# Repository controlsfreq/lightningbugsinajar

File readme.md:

# Readme #

The Lightning Bugs in a Jar (LBJ) application is used to control up to 8 LEDs and flash them randomly as if they were lightning bugs.

## Toolchain ##

* [WinAVR](http://sourceforge.net/projects/winavr/files/) - Compiler, linker, archiver, etc.
* [AvrDude](http://www.nongnu.org/avrdude/) - Programmer interface application.
* [LibUSB](http://sourceforge.net/projects/libusb-win32/) - USB driver for AvrDude which allows it to interface with the AVRISP mkII. Running `bin/inf-wizard.exe` will create a driver for a connected AVRISP mkII and install it.
* [Cygwin](https://www.cygwin.com) - Provides Make and a build environment.

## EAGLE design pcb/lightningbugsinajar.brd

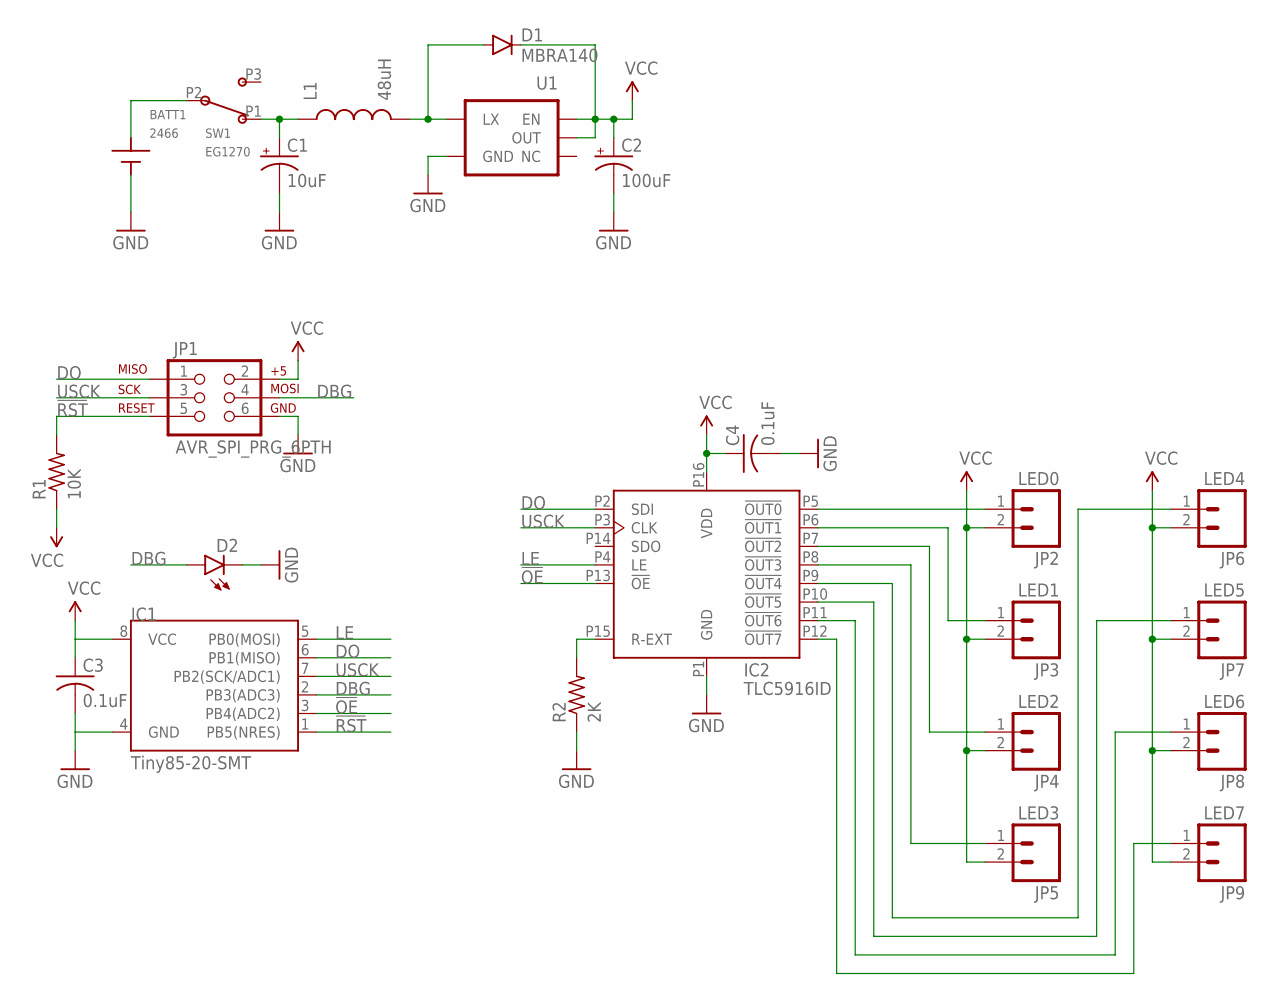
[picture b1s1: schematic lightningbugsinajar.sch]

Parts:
BATT1: 2466
C1: 10uF; EIA3528
C2: 100uF; EIA3528
C3, C4: 0.1uF; C0805
D1: MBRA140; SMA-DIODE
D2: LED3MM
IC1: Tiny85-20-SMT; SO08-EIAJ
IC2: TLC5916ID; SOIC-16
JP1: AVR_SPI_PRG_6PTH; 2X3
JP2: LED0; 1X02
JP3: LED1; 1X02
JP4: LED2; 1X02
JP5: LED3; 1X02
JP6: LED4; 1X02
JP7: LED5; 1X02
JP8: LED6; 1X02
JP9: LED7; 1X02
L1: 48uH; CR54
R1: 10K; R0805
R2: 2K; R0805
SW1: EG1270
U1: V_REG_NCP1400SOT23-5; SOT23-5

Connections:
3: SW1.P3 (3)
!OE: IC1.3 (PB4(ADC2)), IC2.P13 (!OE)
!RST: IC1.1 (PB5(NRES)), JP1.5, R1.2
DBG: D2.A, IC1.2 (PB3(ADC3)), JP1.4
DO: IC1.6 (PB1(MISO)), IC2.P2 (SDI), JP1.1
GND: BATT1.NEG, C1.C (-), C2.C (-), C3.2, C4.2, D2.K (C), IC1.4 (GND), IC2.P1 (GND), JP1.6, R2.1, U1.4 (GND)
LE: IC1.5 (PB0(MOSI)), IC2.P4 (LE)
unnamed: C1.A (+), L1.P$1 (1), SW1.P1 (1)
unnamed: D1.A, L1.P$2 (2), U1.5 (LX)
unnamed: IC2.P5 (!OUT0), JP2.1
unnamed: IC2.P15 (R-EXT), R2.2
unnamed: IC2.P6 (!OUT1), JP3.1
unnamed: IC2.P7 (!OUT2), JP4.1
unnamed: IC2.P8 (!OUT3), JP5.1
unnamed: IC2.P9 (!OUT4), JP6.1
unnamed: IC2.P10 (!OUT5), JP7.1
unnamed: BATT1.POS, SW1.P2 (COM)
unnamed: IC2.P11 (!OUT6), JP8.1
unnamed: IC2.P12 (!OUT7), JP9.1
USCK: IC1.7 (PB2(SCK/ADC1)), IC2.P3 (CLK), JP1.3
VCC: C2.A (+), C3.1, C4.1, D1.C, IC1.8 (VCC), IC2.P16 (VDD), JP1.2, JP2.2, JP3.2, JP4.2, JP5.2, JP6.2, JP7.2, JP8.2, JP9.2, R1.1, U1.1 (EN), U1.2 (OUT)

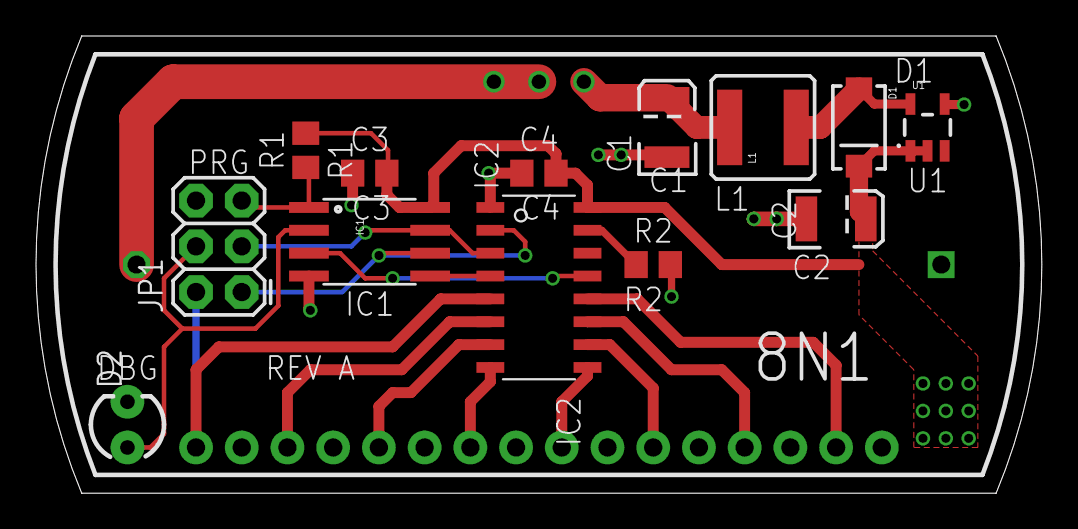
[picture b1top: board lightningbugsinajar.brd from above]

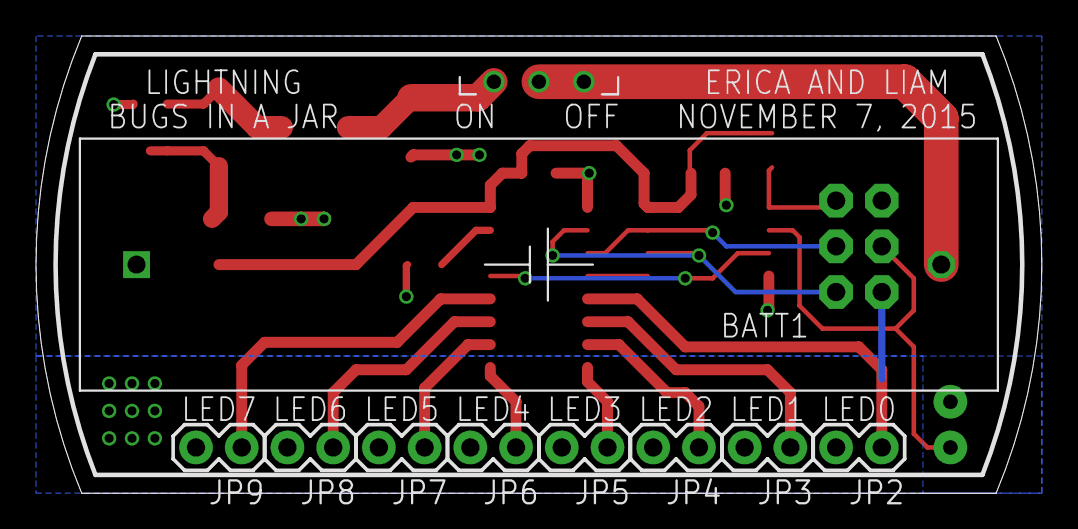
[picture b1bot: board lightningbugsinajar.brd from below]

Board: 2 copper layers, 55.9 x 25.4 mm, 23 parts (10 on the bottom side), 20 nets.

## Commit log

2015-03-15 :lollipop: Added .gitattributes & .gitignore files
2015-08-24 ### Build System and Project Structure ###
    * Added basic Makefile based build system.
    * Added basic project files (including simple main.c)
    * Tested build system to produce x86 executable (hello world)
2015-08-29 Hello World Application
    * Changed Makefile to build embedded project. Builds all objects, then
    an elf file, then converts it to an Intel hex.
    * Changed main to flash an LED connected on PB3.
    * Added a readme.md which describes the required toolchain (including
    usb driver for the AVRISP mkII).
2015-08-29 Release 0.1.0
    * Updated version numbers
2015-08-30 Pin Driver
    * Added pin driver. AVR implementation only supports bank B. Tested
    toggle, assert, and deassert functions.
2015-08-30 SPI Driver
    * Added an SPI driver. Sends SPI data in mode CPOL=1, CPHA=1 (compatible
    with the TLC591x).
    * Tested by sending data and reading with a Saleae Logic analyzer.
2015-08-30 TLC591x Driver and bug fixes
    * Added a TLC591x driver which uses the SPI driver to send output values
    to the TLC591x chip. Controls the LE and !OE lines as necessary.
    * Bug fixes in the SPI driver:
    * Return value wasn't correct.
    * Initial register value wasn't correct.
2015-08-30 Release v0.2.0
    * Bump version number.
2015-09-17 Timer1, Linker Script, Fuse Bits
    * Added general Timer interface.
    * Added AVR timer1 implementation.
    * Added linker script with attiny85 memory settings (avr-gcc uses a
    generic script with inflated memory regions).
    * Added command line options to program fuse bits from Makefile.
2016-08-01 Final product
    Finished all work. And now we're married!
2016-08-02 Adds Eagle CAD files

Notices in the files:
parts and their libraries:
SparkFun-Passives: Licensing: Creative Commons ShareAlike 4.0 International - https://creativecommons.org/licenses/by-sa/4.0
